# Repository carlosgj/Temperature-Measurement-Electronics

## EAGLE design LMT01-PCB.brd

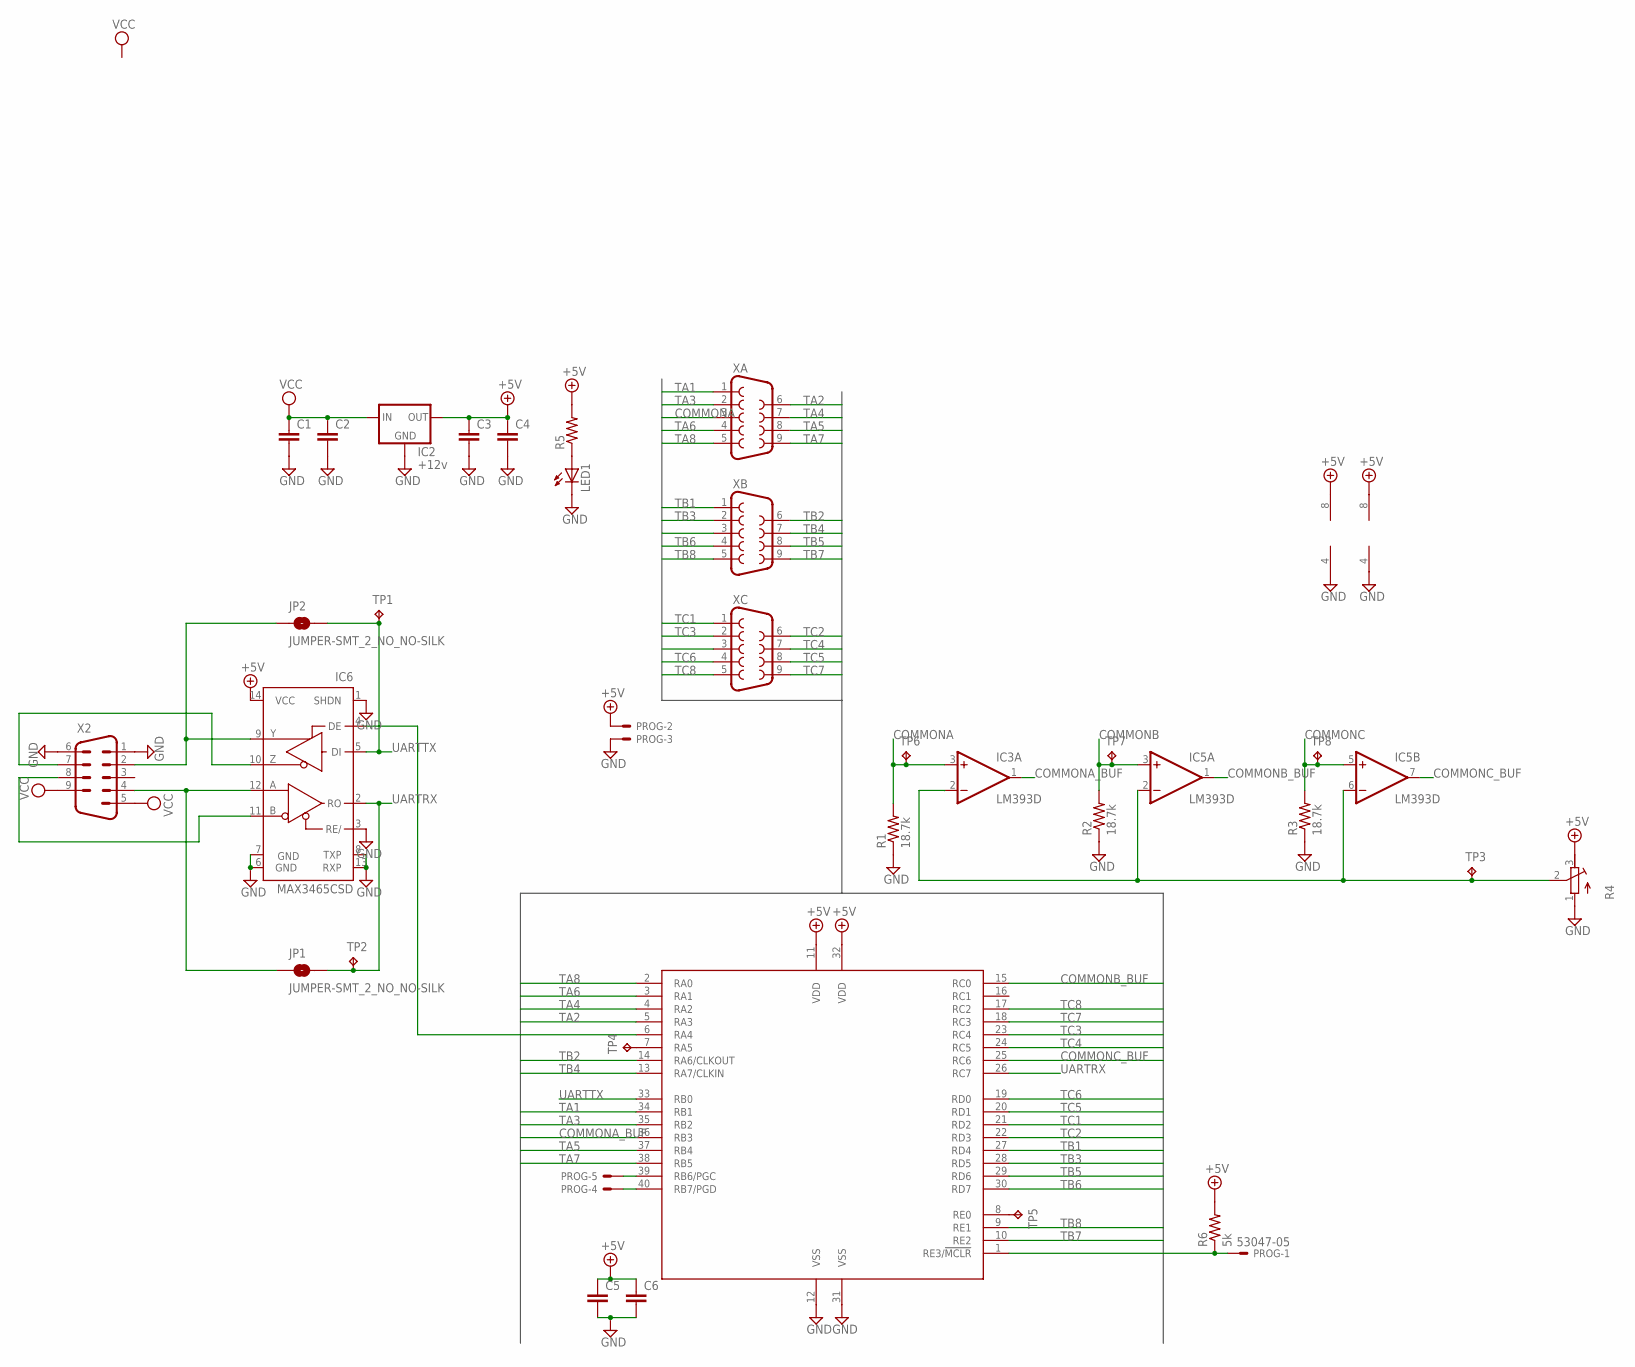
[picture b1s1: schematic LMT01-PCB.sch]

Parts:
C1, C2, C3, C4, C5, C6: C-EUC1206; C1206
IC1: PIC18F47Q84; DIL40
IC2: +12v; TO-252
IC3, IC5: LM393D; SO08
IC6: MAX3465CSD; SO14
JP1, JP2: JUMPER-SMT_2_NO_NO-SILK; SMT-JUMPER_2_NO_NO-SILK
LED1: LEDCHIPLED_1206; CHIPLED_1206
PROG: 53047-05
R1, R2, R3: 18.7k; R1206
R4: R-TRIMM4G/J; RTRIM4G/J
R5: R-US_R1206; R1206
R6: 5k; R1206
TP1, TP2, TP3, TP4, TP5, TP6, TP7, TP8: TPB1,27; B1,27
X2: M09HP
XA: F09HP
XB: F09HP
XC: F09HP

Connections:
+5V: C3.1, C4.1, C5.1, C6.1, IC1.11 (VDD), IC1.32 (VDD), IC2.2 (OUT), IC3.8 (V+), IC5.8 (V+), IC6.14 (VCC), PROG.2, R4.3 (E), R5.2, R6.2
COMMONA: IC3.3 (+IN), R1.2, TP6.TP, XA.3
COMMONA_BUF: IC1.36 (RB3), IC3.1 (OUT)
COMMONB: IC5.3 (+IN), R2.2, TP7.TP, XB.3
COMMONB_BUF: IC1.15 (RC0), IC5.1 (OUT)
COMMONC: IC5.5 (+IN), R3.2, TP8.TP, XC.3
COMMONC_BUF: IC1.25 (RC6), IC5.7 (OUT)
GND: C1.2, C2.2, C3.2, C4.2, C5.2, C6.2, IC1.12 (VSS), IC1.31 (VSS), IC2.3 (GND), IC3.4 (V-), IC5.4 (V-), IC6.1 (SHDN), IC6.3 (RE/), IC6.6 (GND), IC6.7 (GND), IC6.8 (TXP), IC6.13 (RXP), LED1.C, PROG.3, R1.1, R2.1, R3.1, R4.1 (A), X2.1, X2.6
unnamed: IC1.1 (RE3/!MCLR), PROG.1, R6.1
unnamed: IC1.40 (RB7/PGD), PROG.4
unnamed: IC1.39 (RB6/PGC), PROG.5
unnamed: IC3.2 (-IN), IC5.2 (-IN), IC5.6 (-IN), R4.2 (S), TP3.TP
unnamed: LED1.A, R5.1
unnamed: IC1.7 (RA5), TP4.TP
unnamed: IC1.8 (RE0), TP5.TP
unnamed: IC1.6 (RA4), IC6.4 (DE)
RX+: IC6.12 (A), JP1.1, X2.4
RX-: IC6.11 (B), X2.8
TA1: IC1.34 (RB1), XA.1
TA2: IC1.5 (RA3), XA.6
TA3: IC1.35 (RB2), XA.2
TA4: IC1.4 (RA2), XA.7
TA5: IC1.37 (RB4), XA.8
TA6: IC1.3 (RA1), XA.4
TA7: IC1.38 (RB5), XA.9
TA8: IC1.2 (RA0), XA.5
TB1: IC1.27 (RD4), XB.1
TB2: IC1.14 (RA6/CLKOUT), XB.6
TB3: IC1.28 (RD5), XB.2
TB4: IC1.13 (RA7/CLKIN), XB.7
TB5: IC1.29 (RD6), XB.8
TB6: IC1.30 (RD7), XB.4
TB7: IC1.10 (RE2), XB.9
TB8: IC1.9 (RE1), XB.5
TC1: IC1.21 (RD2), XC.1
TC2: IC1.22 (RD3), XC.6
TC3: IC1.23 (RC4), XC.2
TC4: IC1.24 (RC5), XC.7
TC5: IC1.20 (RD1), XC.8
TC6: IC1.19 (RD0), XC.4
TC7: IC1.18 (RC3), XC.9
TC8: IC1.17 (RC2), XC.5
TX+: IC6.9 (Y), JP2.1, X2.2
TX-: IC6.10 (Z), X2.7
UARTRX: IC1.26 (RC7), IC6.2 (RO), JP1.2, TP2.TP
UARTTX: IC1.33 (RB0), IC6.5 (DI), JP2.2, TP1.TP
VCC: C1.1, C2.1, IC2.1 (IN), X2.5, X2.9

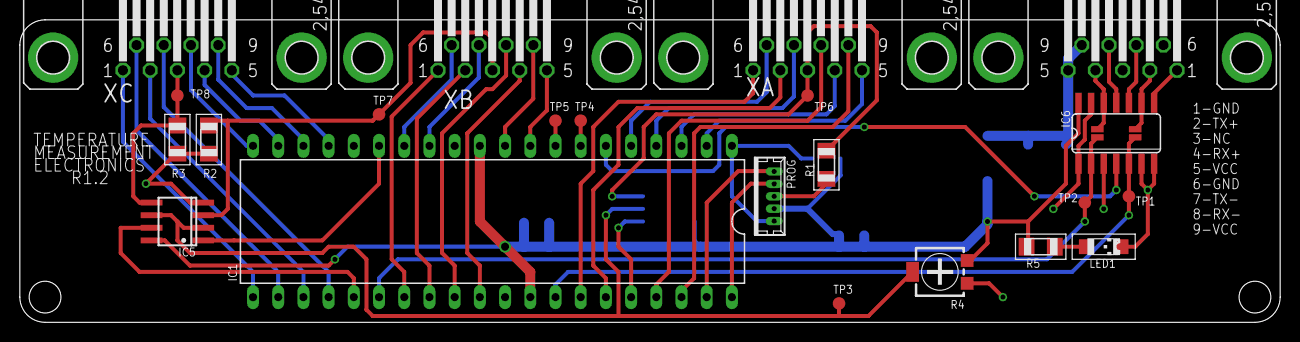
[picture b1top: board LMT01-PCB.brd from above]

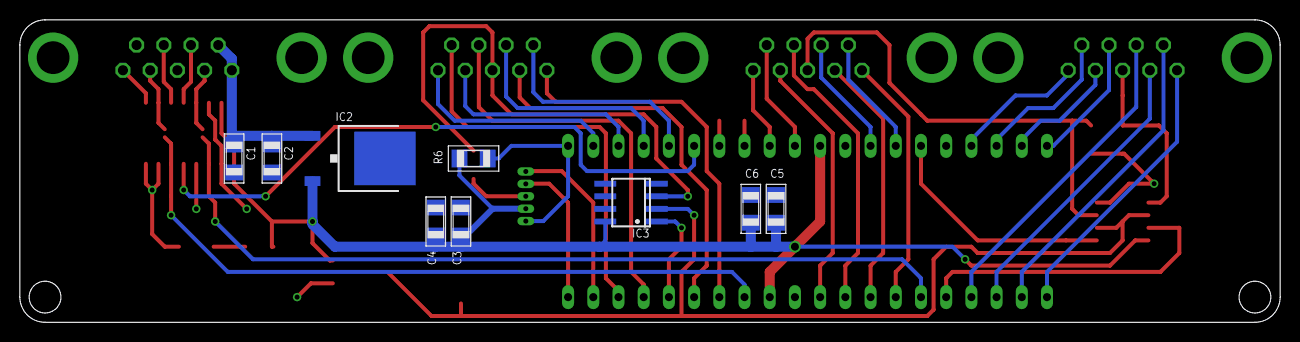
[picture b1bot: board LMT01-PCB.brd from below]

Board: 2 copper layers, 127.0 x 30.5 mm, 33 parts (9 on the bottom side), 47 nets.

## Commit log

2021-03-15 Switching to big PIC
2021-03-16 PIC18
2021-03-16 Initial code work
2021-03-16 Code work
2021-03-21 Adding optional comparators and voltage reference
2021-03-21 Adding power LED
2021-03-23 Upgrading to PIC18F47Q84
2021-03-23 Pin names
2021-03-24 Implements high-water marks and updates for PIC18
2021-03-30 Create LICENSE
2021-04-01 Working on code
2021-04-18 Fixing ms timer bug
2021-04-18 Moving high-water marks to commError
2021-04-18 Implementing timed main loop & LOOPOUT toggle
2021-04-18 Adding debug patterns for HWMs
2021-04-18 Adding loop overrun monitor
2021-04-18 Working on LMT01 code
2021-04-18 Work on LMT01 code
2021-04-18 COSMOS stuff
2021-04-18 LMT01 code
2021-04-18 Adding temperature telemetry
2021-04-18 Adding seconds telemetry
2021-04-20 Swapping counters
2021-05-12 Adding test points
2021-05-12 Adding more test points and deleting jumpers
2021-07-23 Adding RS-485 capability
2021-07-23 Adding pullup resistor on MCLR

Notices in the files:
parts and their libraries:
SparkFun-Jumpers: Licensing: Creative Commons ShareAlike 4.0 International - https://creativecommons.org/licenses/by-sa/4.0
